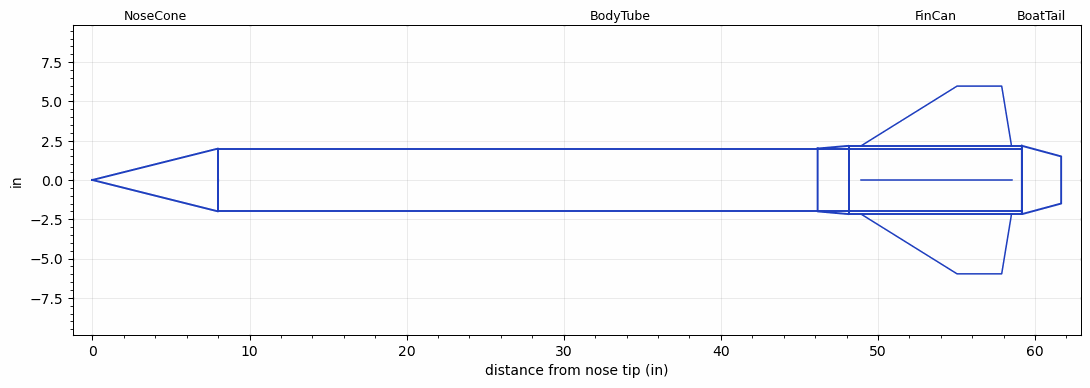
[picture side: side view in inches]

<RASAeroDocument>
 <FileVersion>2</FileVersion>
 <RocketDesign>
  <NoseCone>
   <Length>8</Length>
   <Diameter>4</Diameter>
   <Shape>Power Law</Shape>
   <BluntRadius>0.0825</BluntRadius>
   <Location>0</Location>
   <PowerLaw>1</PowerLaw>
  </NoseCone>
  <BodyTube>
   <Length>51.16</Length>
   <Diameter>4</Diameter>
   <Location>8</Location>
  </BodyTube>
  <FinCan>
   <Length>11</Length>
   <Diameter>4.35</Diameter>
   <InsideDiameter>4</InsideDiameter>
   <Location>59.16</Location>
   <ShoulderLength>2</ShoulderLength>
   <Offset>-11</Offset>
   <Fin>
    <Count>4</Count>
    <Chord>9.57</Chord>
    <Span>3.8</Span>
    <SweepDistance>6.105</SweepDistance>
    <TipChord>2.84</TipChord>
    <Thickness>0.25</Thickness>
    <LERadius>0.08</LERadius>
    <Location>10.23</Location>
    <AirfoilSection>Hexagonal</AirfoilSection>
    <FX1>0.5</FX1>
    <FX3>0.5</FX3>
   </Fin>
  </FinCan>
  <BoatTail>
   <Length>2.5</Length>
   <Diameter>4.35</Diameter>
   <RearDiameter>3</RearDiameter>
   <Location>59.16</Location>
  </BoatTail>
  <Surface>Cast Iron (Very Rough)</Surface>
  <ModifiedBarrowman>True</ModifiedBarrowman>
  <Turbulence>True</Turbulence>
  <UseBooster1>False</UseBooster1>
  <UseBooster2>False</UseBooster2>
 </RocketDesign>
 <LaunchSite>
  <Altitude>3000</Altitude>
  <Pressure>0</Pressure>
  <RodAngle>2</RodAngle>
  <RodLength>18</RodLength>
  <Temperature>85</Temperature>
  <WindSpeed>8</WindSpeed>
 </LaunchSite>
 <Recovery>
  <Altitude1>1000</Altitude1>
  <Altitude2>1000</Altitude2>
  <DeviceType1>None</DeviceType1>
  <DeviceType2>None</DeviceType2>
  <Event1>False</Event1>
  <Event2>False</Event2>
  <Size1>1</Size1>
  <Size2>1</Size2>
  <EventType1>None</EventType1>
  <EventType2>None</EventType2>
  <CD1>1.33</CD1>
  <CD2>1.33</CD2>
 </Recovery>
 <SimulationList>
  <Simulation>
   <SustainerEngine>O4400  (O4400)</SustainerEngine>
   <SustainerLaunchWt>63</SustainerLaunchWt>
   <SustainerNozzleDiameter>3.8</SustainerNozzleDiameter>
   <SustainerCG>26.11</SustainerCG>
   <SustainerIgnitionDelay>15</SustainerIgnitionDelay>
   <Booster1Engine>Q10000  (Q10000)</Booster1Engine>
   <Booster1LaunchWt>167</Booster1LaunchWt>
   <Booster1SeparationDelay>0</Booster1SeparationDelay>
   <Booster1IgnitionDelay>0</Booster1IgnitionDelay>
   <Booster1CG>105.13</Booster1CG>
   <Booster1NozzleDiameter>5.3</Booster1NozzleDiameter>
   <IncludeBooster1>True</IncludeBooster1>
   <Booster2Delay>0</Booster2Delay>
   <IncludeBooster2>False</IncludeBooster2>
   <TimetoApogee>220.9127</TimetoApogee>
   <MaxAltitude>673488.4</MaxAltitude>
   <MaxVelocity>6297.921</MaxVelocity>
  </Simulation>
  <Simulation>
   <SustainerEngine>O4400  (O4400)</SustainerEngine>
   <SustainerLaunchWt>63</SustainerLaunchWt>
   <SustainerNozzleDiameter>3.8</SustainerNozzleDiameter>
   <SustainerCG>26.11</SustainerCG>
   <SustainerIgnitionDelay>0</SustainerIgnitionDelay>
   <Booster1SeparationDelay>0</Booster1SeparationDelay>
   <Booster1IgnitionDelay>0</Booster1IgnitionDelay>
   <IncludeBooster1>False</IncludeBooster1>
   <Booster2Delay>0</Booster2Delay>
   <IncludeBooster2>False</IncludeBooster2>
   <TimetoApogee>46.64818</TimetoApogee>
   <MaxAltitude>43434.07</MaxAltitude>
   <MaxVelocity>2935.559</MaxVelocity>
  </Simulation>
 </SimulationList>
</RASAeroDocument>
